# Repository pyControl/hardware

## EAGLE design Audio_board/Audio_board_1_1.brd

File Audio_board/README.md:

# Audio board

An audio amplifier board for driving a speaker to produce auditory stimuli. The board uses the micropython DAC for stimulus generation. The audio board must be plugged into a port on the breakout board which supports DAC output and I2C serial communication (used to set the volume). Up to two audio boards can be used with a single breakout board allowing two speakers to be driven independently.

[documentation](https://pycontrol.readthedocs.io/en/latest/user-guide/hardware/#audio-board)

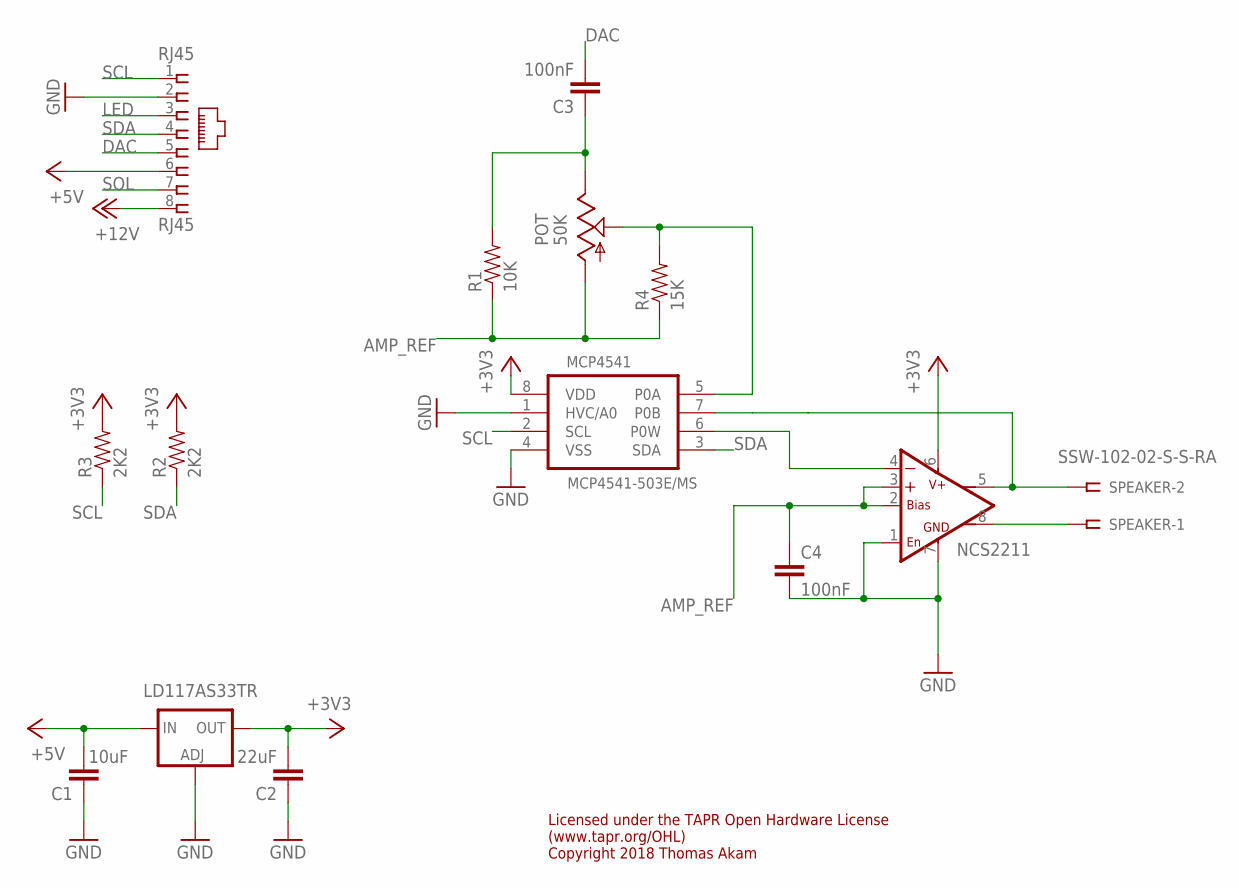
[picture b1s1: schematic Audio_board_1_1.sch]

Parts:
C1: 10uF; C1206
C2: 22uF; C1206
C3, C4: 100nF; C0805
LD117: LD117AS33TR; SOT223
MCP4541: MCP4541-503E/MS; SOP65P490X110-8N
NCS2211: NCS22111M; SO08
POT: 50K; RS3
R1: 10K; 0805
R2, R3: 2K2; 0805
R4: 15K; 0805
RJ45: RJ45; RJ45-NO-SHIELD-VERTICAL
SPEAKER: SSW-102-02-S-S-RA

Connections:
+3V3: C2.2, LD117.4 (OUT), MCP4541.8 (VDD), NCS2211.6 (VS), R2.2, R3.2
+5V: C1.2, LD117.3 (IN), RJ45.6
+12V: RJ45.8
AMP_REF: C4.1, NCS2211.2 (BIAS), NCS2211.3 (+IN), POT.A, R1.1, R4.1
DAC: C3.2, RJ45.5
GND: C1.1, C2.1, C4.2, LD117.1 (ADJ), MCP4541.1 (HVC/A0), MCP4541.4 (VSS), NCS2211.1 (ENABLE), NCS2211.7 (GND), RJ45.2
LED: RJ45.3
unnamed: NCS2211.8 (-OUT), SPEAKER.1
SCL: MCP4541.2 (SCL), R3.1, RJ45.1
SDA: MCP4541.3 (SDA), R2.1, RJ45.4
SIG1: C3.1, POT.E, R1.2
SIG2: MCP4541.5 (P0A), POT.S, R4.2
SIG3: MCP4541.6 (P0W), NCS2211.4 (-IN)
SOL: RJ45.7
SPEAKER+: MCP4541.7 (P0B), NCS2211.5 (+OUT), SPEAKER.2

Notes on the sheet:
Licensed under the TAPR Open Hardware License (www.tapr.org/OHL) Copyright 2018 Thomas Akam

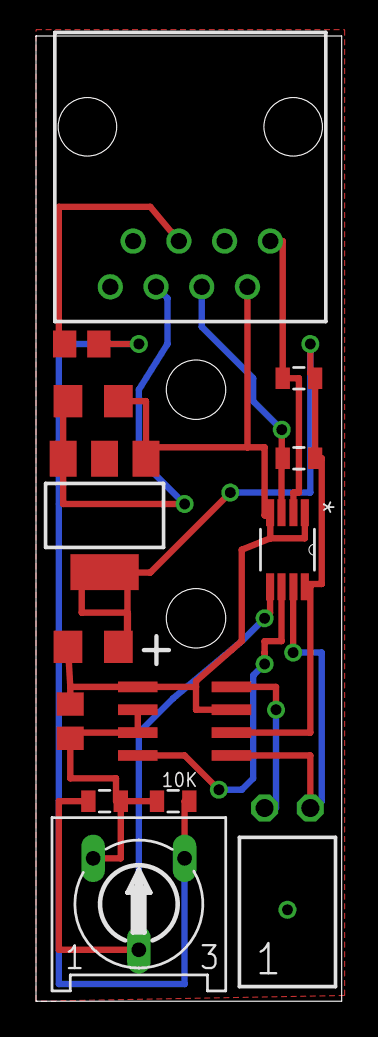
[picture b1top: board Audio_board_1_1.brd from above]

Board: 2 copper layers, 17.0 x 53.6 mm, 14 parts (0 on the bottom side), 12 nets.

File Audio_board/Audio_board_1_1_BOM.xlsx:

Part | Value | Device | Package | Description | MF | MPN | OC_FARNELL
C1 | 10uF | - | 1206 | Capacitor | MULTICOMP | MC1206X106K160CT | 2112752
C2 | 22uF | - | 1206 | Capacitor | KEMET | T491A226K010AT | 1457420
C3 | 100nF | - | 0805 | Capacitor | MULTICOMP | MC0805B104K500CT | 1759265
C4 | 100nF | - | 0805 | Capacitor | MULTICOMP | MC0805B104K500CT | 1759265
LD117 | - | AP1117E33G-13 | SOT223 | LDO Vreg | DIODES INC | AP1117E33G-13 | 1825291
MCP4541 | 50K | MCP4541-503E/MS | MSOP8 | Digital POT | MICROCHIP | MCP4541-503E/MS | 1840713
NCS2211 | - | NCS2211DR2G | SO08 | Audio Power Amp | ON SEMICONDUCTOR | NCS2211DR2G | 2464727
R1 | 10K | - | 0805 | Resistor 0805 | BOURNS | CR0805-FX-1002ELF | 1612522
R2 | 2K2 | - | 0805 | Resistor 0805 | Multicomp | MCWR08X2201FTL | 2447623
R3 | 2K2 | - | 0805 | Resistor 0805 | Multicomp | MCWR08X2201FTL | 2447623
R4 | 15K | - | 0805 | Resistor 0805 | Multicomp | MC01W0805115K | 9332618
POT | 50K | - | - | POTENTIOMETER | BOURNS | 3386F-1-503TLF | 9354727
RJ45 | - | RJ45Horisontal | - | RJ45Horisontal | TE CONNECTIVITY | 215877-1 | 3363144
SPKR | - | - | - | 2x1 Receptacle, right angle | SAMTEC | SSW-102-02-T-S-RA | 1803308
Licensed under the TAPR Open Hardware License
(www.tapr.org/OHL)
Copyright 2018 Thomas Akam

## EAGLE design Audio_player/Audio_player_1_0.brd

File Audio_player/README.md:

# Audio player

An audio board for pyControl which uses a [DF player](https://www.dfrobot.com/wiki/index.php/DFPlayer_Mini_SKU:DFR0299) module to play wav files from an SD card. The board has two speaker outputs which can be independently enabled/disabled, allowing stereo wav files to be played, or mono wav files to be played from either or both speakers. 

[Documentation](https://pycontrol.readthedocs.io/en/latest/user-guide/hardware/#audio_player)

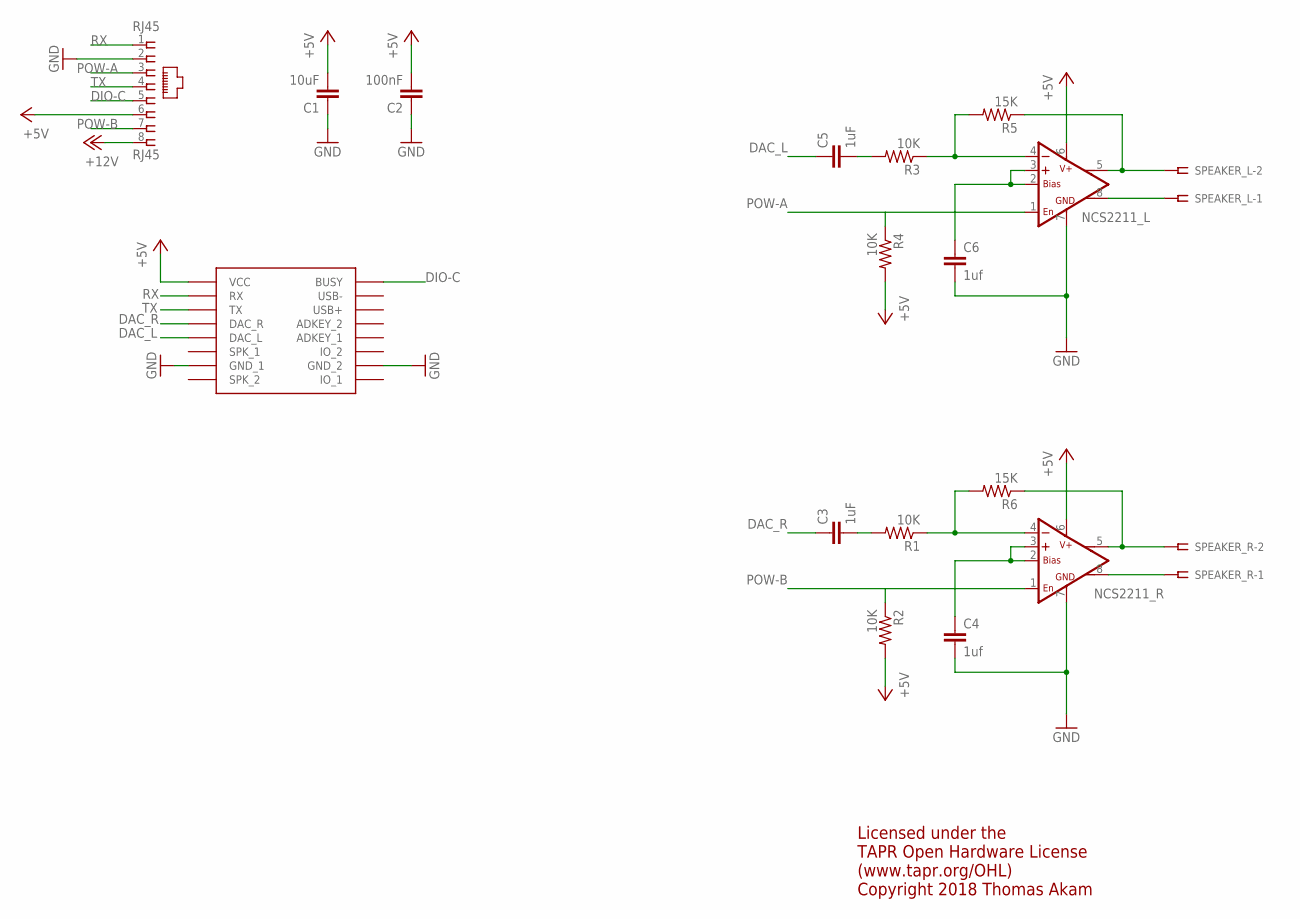
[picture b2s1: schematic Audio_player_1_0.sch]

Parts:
C1: 10uF; C0805
C2: 100nF; C0805
C3, C5: 1uF; C0805
C4, C6: 1uf; C0805
NCS2211_L, NCS2211_R: NCS22111M; SO08
R1, R2, R3, R4: 10K; 0805
R5, R6: 15K; 0805
RJ45: RJ45; RJ45-NO-SHIELD-VERTICAL
SPEAKER_L: SSW-102-02-S-S-RA
SPEAKER_R: SSW-102-02-S-S-RA
U$1: DFPLAYER

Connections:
+5V: C1.2, C2.2, NCS2211_L.6 (VS), NCS2211_R.6 (VS), R2.2, R4.2, RJ45.6, U$1.VCC
+12V: RJ45.8
AMP_REF: C4.1, NCS2211_R.2 (BIAS), NCS2211_R.3 (+IN)
AMP_REF1: C6.1, NCS2211_L.2 (BIAS), NCS2211_L.3 (+IN)
DAC_L: C5.1, U$1.DAC_L
DAC_R: C3.1, U$1.DAC_R
DIO-C: RJ45.5, U$1.BUSY
GND: C1.1, C2.1, C4.2, C6.2, NCS2211_L.7 (GND), NCS2211_R.7 (GND), RJ45.2, U$1.GND_1, U$1.GND_2
unnamed: NCS2211_L.8 (-OUT), SPEAKER_L.1
unnamed: NCS2211_R.8 (-OUT), SPEAKER_R.1
unnamed: C3.2, R1.2
unnamed: C5.2, R3.2
POW-A: NCS2211_L.1 (ENABLE), R4.1, RJ45.3
POW-B: NCS2211_R.1 (ENABLE), R2.1, RJ45.7
RX: RJ45.1, U$1.RX
SIG1: NCS2211_L.4 (-IN), R3.1, R5.2
SIG3: NCS2211_R.4 (-IN), R1.1, R6.2
SPEAKER+: NCS2211_R.5 (+OUT), R6.1, SPEAKER_R.2
SPEAKER+1: NCS2211_L.5 (+OUT), R5.1, SPEAKER_L.2
TX: RJ45.4, U$1.TX

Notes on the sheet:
Licensed under the TAPR Open Hardware License (www.tapr.org/OHL) Copyright 2018 Thomas Akam

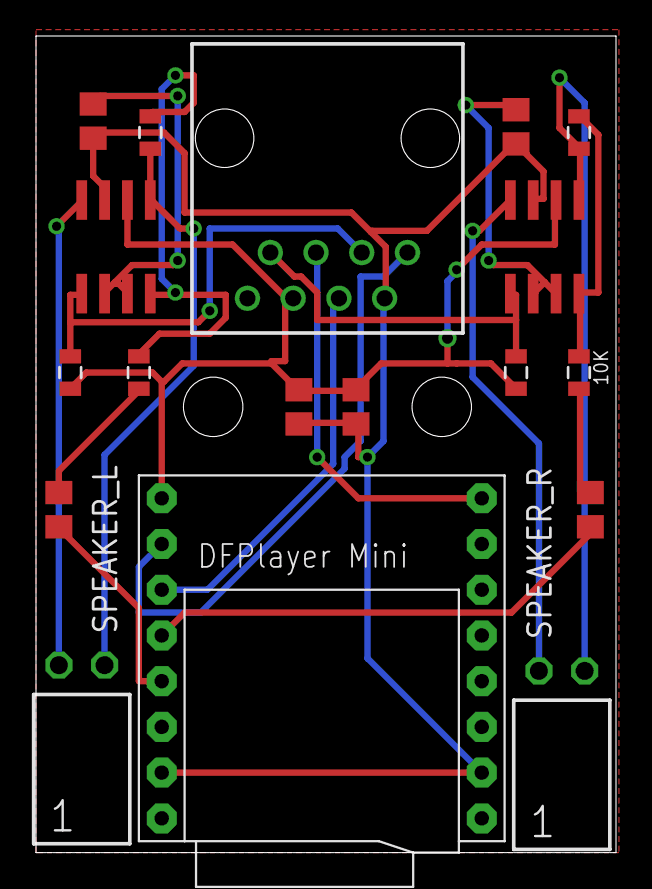
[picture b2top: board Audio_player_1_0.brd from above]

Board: 2 copper layers, 32.2 x 45.4 mm, 18 parts (0 on the bottom side), 19 nets.

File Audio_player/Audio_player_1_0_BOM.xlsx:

Part | Value | Device | Package | Description | MF | MPN | OC_FARNELL
C1 | 10uF | - | 0805 | Capacitor | MURATA | GCM21BR70J106KE22L | 2470434
C2 | 100nF | - | 0805 | Capacitor | MULTICOMP | MC0805B104K500CT | 1759265
C3 | 1uF | - | 0805 | Capacitor | MULTICOMP | MC0805B105K100CT | 2320857
C4 | 1uF | - | 0805 | Capacitor | MULTICOMP | MC0805B105K100CT | 2320857
C5 | 1uF | - | 0805 | Capacitor | MULTICOMP | MC0805B105K100CT | 2320857
C5 | 1uF | - | 0805 | Capacitor | MULTICOMP | MC0805B105K100CT | 2320857
R1 | 10K | - | 0805 | Resistor | MULTICOMP | MCWR08X1002FTL | 2447553
R2 | 10K | - | 0805 | Resistor | MULTICOMP | MCWR08X1002FTL | 2447553
R3 | 10K | - | 0805 | Resistor | MULTICOMP | MCWR08X1002FTL | 2447553
R4 | 10K | - | 0805 | Resistor | MULTICOMP | MCWR08X1002FTL | 2447553
R5 | 15K | - | 0805 | Resistor | MULTICOMP | MCWR08X1502FTL | 2447575
R6 | 15K | - | 0805 | Resistor | MULTICOMP | MCWR08X1502FTL | 2447575
NCS2211_L | - | NCS2211DR2G | SO08 | Audio Power Amp | ON SEMICONDUCTOR | NCS2211DR2G | 2464727
NCS2211_R | - | NCS2211DR2G | SO08 | Audio Power Amp | ON SEMICONDUCTOR | NCS2211DR2G | 2464727
RJ45 |  | - | - | RJ45 con. vertical | TE CONNECTIVITY | 5556416-1 | 1773034
SPEAKER_L | - | - | - | 2x1 Receptacle, right angle | SAMTEC | SSW-102-02-T-S-RA | 1803308
SPEAKER_R | - | - | - | 2x1 Receptacle, right angle | SAMTEC | SSW-102-02-T-S-RA | 1803308
DFPLAYER_CON_1 | - | - | - | 8 Way female header | MULTICOMP | 2212S-08SG-85 | 1593463
DFPLAYER_CON_2 | - | - | - | 8 Way female header | MULTICOMP | 2212S-08SG-85 | 1593463
DFPlayer | - | - | - | DFPlayer module | DFRobot | DFR0299 | -
Licensed under the TAPR Open Hardware License
(www.tapr.org/OHL)
Copyright 2018 Thomas Akam

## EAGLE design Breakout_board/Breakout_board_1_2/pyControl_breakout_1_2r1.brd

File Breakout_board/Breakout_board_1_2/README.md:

# Breakout board 1.2

This folder contains design files for version 1.2 of the pyControl breakout board.

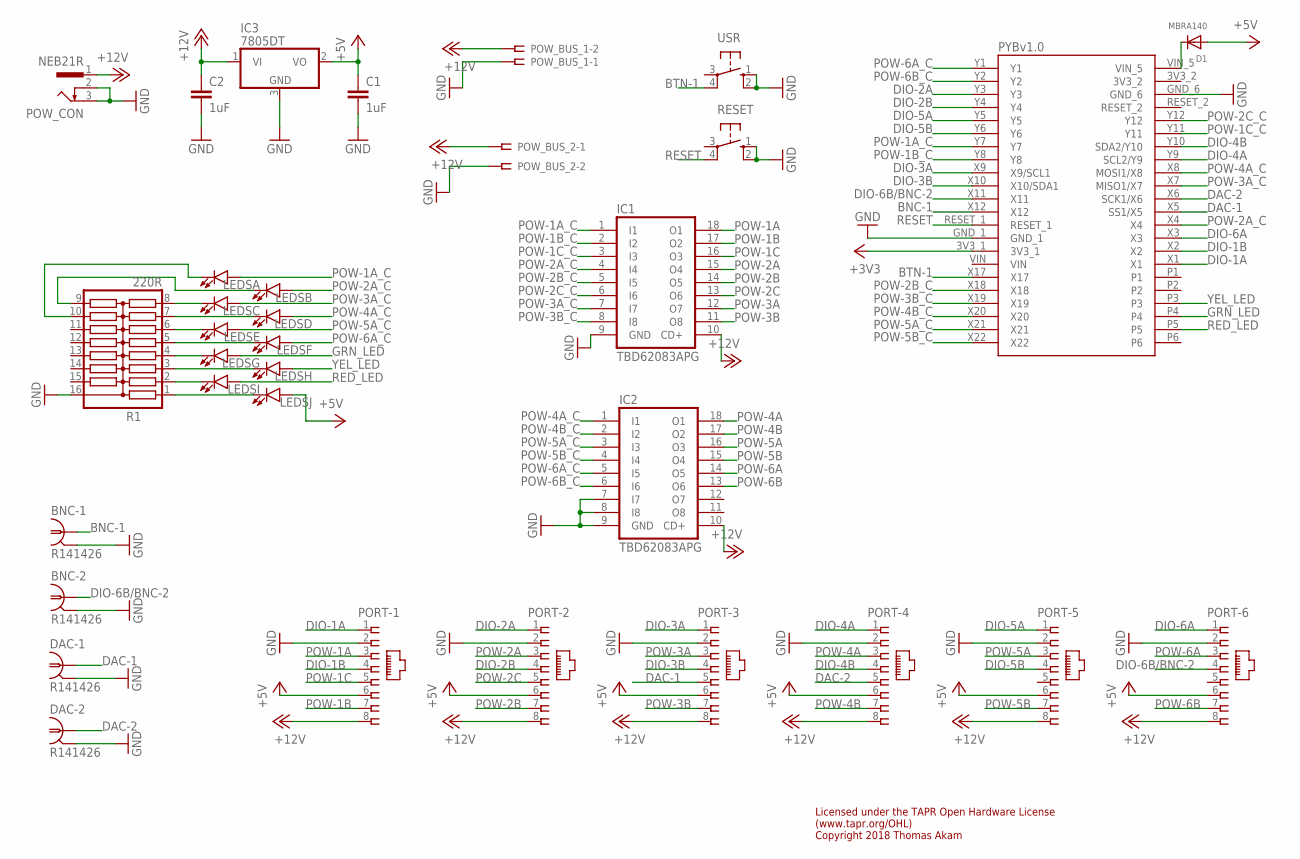
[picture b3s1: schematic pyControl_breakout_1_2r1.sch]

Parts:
BNC-1, BNC-2: R141426
C1, C2: 1uF; C1206
D1: MBRA140; SOD-123
DAC-1, DAC-2: R141426
IC1, IC2: TBD62083APG; DIL18
IC3: 7805DT; TO252
LEDS: LED_BARGRAPH_10; LED_BARGAPH_10
PORT-1, PORT-2, PORT-3, PORT-4, PORT-5, PORT-6: RJ45VERTICAL; RJ45-NO-SHIELD-VERTICAL
POW_BUS_1, POW_BUS_2: SSW-102-02-S-S-RA
POW_CON: NEB21R
PYBOARD: PYBOARD-REDUCED-2
R1: 220R; SO16
RESET: 40-XX; B3F-40XX; MPN B3F-4000
USR: 40-XX; B3F-40XX

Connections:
+3V3: PYBOARD.3V3_1
+5V: C1.1, D1.A, IC3.2 (VO), LEDS.10 (A), PORT-1.6, PORT-2.6, PORT-3.6, PORT-4.6, PORT-5.6, PORT-6.6
+12V: C2.1, IC1.10 (CD+), IC2.10 (CD+), IC3.1 (VI), PORT-1.8, PORT-2.8, PORT-3.8, PORT-4.8, PORT-5.8, PORT-6.8, POW_BUS_1.2, POW_BUS_2.1, POW_CON.1
BNC-1: BNC-1.1, PYBOARD.X12
BTN-1: PYBOARD.X17, USR.4 (P1)
DAC-1: DAC-1.1, PORT-3.5, PYBOARD.X5 (SS1/X5)
DAC-2: DAC-2.1, PORT-4.5, PYBOARD.X6 (SCK1/X6)
DIO-1A: PORT-1.1, PYBOARD.X1
DIO-1B: PORT-1.4, PYBOARD.X2
DIO-2A: PORT-2.1, PYBOARD.Y3
DIO-2B: PORT-2.4, PYBOARD.Y4
DIO-3A: PORT-3.1, PYBOARD.X9 (X9/SCL1)
DIO-3B: PORT-3.4, PYBOARD.X10 (X10/SDA1)
DIO-4A: PORT-4.1, PYBOARD.Y9 (SCL2/Y9)
DIO-4B: PORT-4.4, PYBOARD.Y10 (SDA2/Y10)
DIO-5A: PORT-5.1, PYBOARD.Y5
DIO-5B: PORT-5.4, PYBOARD.Y6
DIO-6A: PORT-6.1, PYBOARD.X3
DIO-6B/BNC-2: BNC-2.1, PORT-6.4, PYBOARD.X11
GND: BNC-1.2 (GND), BNC-1.3 (GND), BNC-1.4 (GND), BNC-1.5 (GND), BNC-2.2 (GND), BNC-2.3 (GND), BNC-2.4 (GND), BNC-2.5 (GND), C1.2, C2.2, DAC-1.2 (GND), DAC-1.3 (GND), DAC-1.4 (GND), DAC-1.5 (GND), DAC-2.2 (GND), DAC-2.3 (GND), DAC-2.4 (GND), DAC-2.5 (GND), IC1.9 (GND), IC2.7 (I7), IC2.8 (I8), IC2.9 (GND), IC3.3 (GND), PORT-1.2, PORT-2.2, PORT-3.2, PORT-4.2, PORT-5.2, PORT-6.2, POW_BUS_1.1, POW_BUS_2.2, POW_CON.2, POW_CON.3, PYBOARD.GND_1, PYBOARD.GND_6, R1.16, RESET.1 (S), RESET.2 (S1), USR.1 (S), USR.2 (S1)
GRN_LED: LEDS.7 (A), PYBOARD.P4
unnamed: LEDS.12 (C), R1.2
unnamed: LEDS.19 (C), R1.9
unnamed: LEDS.18 (C), R1.8
unnamed: LEDS.17 (C), R1.7
unnamed: LEDS.16 (C), R1.6
unnamed: LEDS.15 (C), R1.5
unnamed: LEDS.14 (C), R1.4
unnamed: LEDS.13 (C), R1.3
unnamed: LEDS.20 (C), R1.10
unnamed: LEDS.11 (C), R1.1
unnamed: D1.C, PYBOARD.VIN_5
POW-1A: IC1.18 (O1), PORT-1.3
POW-1A_C: IC1.1 (I1), LEDS.1 (A), PYBOARD.Y7
POW-1B: IC1.17 (O2), PORT-1.7
POW-1B_C: IC1.2 (I2), PYBOARD.Y8
POW-1C: IC1.16 (O3), PORT-1.5
POW-1C_C: IC1.3 (I3), PYBOARD.Y11
POW-2A: IC1.15 (O4), PORT-2.3
POW-2A_C: IC1.4 (I4), LEDS.2 (A), PYBOARD.X4
POW-2B: IC1.14 (O5), PORT-2.7
POW-2B_C: IC1.5 (I5), PYBOARD.X18
POW-2C: IC1.13 (O6), PORT-2.5
POW-2C_C: IC1.6 (I6), PYBOARD.Y12
POW-3A: IC1.12 (O7), PORT-3.3
POW-3A_C: IC1.7 (I7), LEDS.3 (A), PYBOARD.X7 (MISO1/X7)
POW-3B: IC1.11 (O8), PORT-3.7
POW-3B_C: IC1.8 (I8), PYBOARD.X19
POW-4A: IC2.18 (O1), PORT-4.3
POW-4A_C: IC2.1 (I1), LEDS.4 (A), PYBOARD.X8 (MOSI1/X8)
POW-4B: IC2.17 (O2), PORT-4.7
POW-4B_C: IC2.2 (I2), PYBOARD.X20
POW-5A: IC2.16 (O3), PORT-5.3
POW-5A_C: IC2.3 (I3), LEDS.5 (A), PYBOARD.X21
POW-5B: IC2.15 (O4), PORT-5.7
POW-5B_C: IC2.4 (I4), PYBOARD.X22
POW-6A: IC2.14 (O5), PORT-6.3
POW-6A_C: IC2.5 (I5), LEDS.6 (A), PYBOARD.Y1
POW-6B: IC2.13 (O6), PORT-6.7
POW-6B_C: IC2.6 (I6), PYBOARD.Y2
RED_LED: LEDS.9 (A), PYBOARD.P5
RESET: PYBOARD.RESET_1, RESET.4 (P1)
YEL_LED: LEDS.8 (A), PYBOARD.P3

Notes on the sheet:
Licensed under the TAPR Open Hardware License (www.tapr.org/OHL) Copyright 2018 Thomas Akam

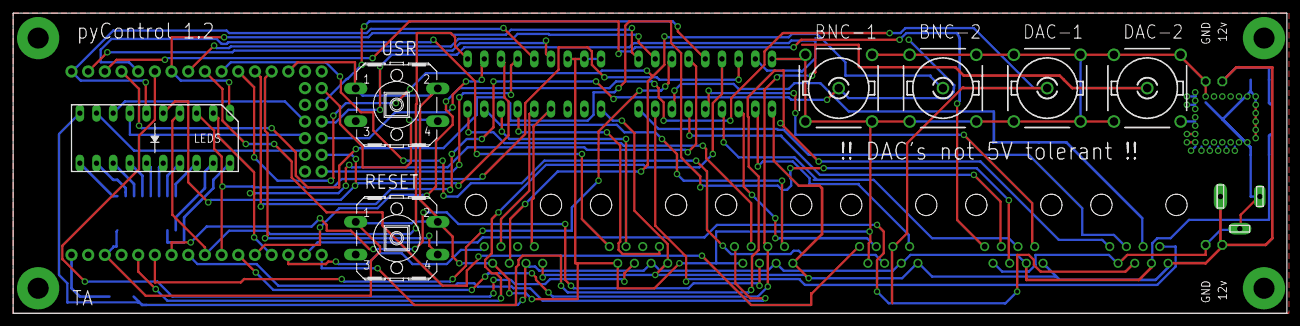
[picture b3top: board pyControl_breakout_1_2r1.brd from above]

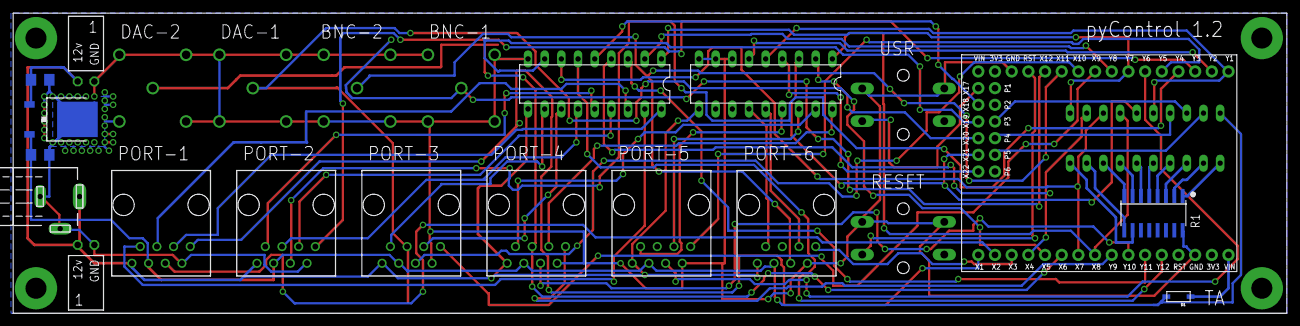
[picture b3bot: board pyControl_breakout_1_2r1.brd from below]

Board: 2 copper layers, 194.0 x 45.7 mm, 24 parts (17 on the bottom side), 62 nets.

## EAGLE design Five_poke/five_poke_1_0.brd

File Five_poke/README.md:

# Five poke

**Assembled**

**PCB**

A set of five nose-pokes mounted in a row on a single PCB and controlled via two behaviour ports.  Each poke consists of an infra-red beam and a stimulus LED that illuminates the back of the poke.

[Documentation](https://pycontrol.readthedocs.io/en/latest/user-guide/hardware/#five-poke)

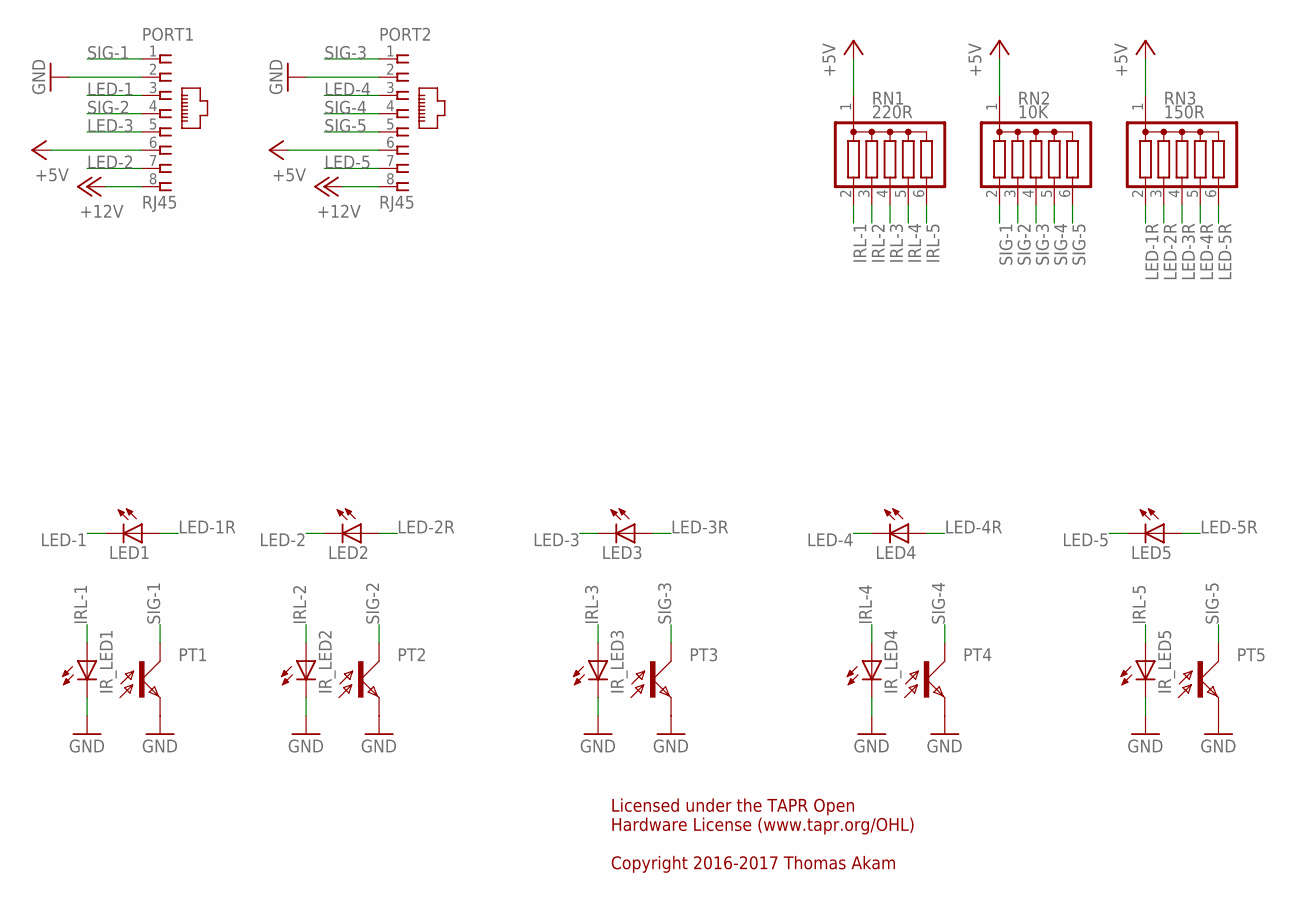
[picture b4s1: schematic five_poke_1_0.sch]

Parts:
IR_LED1, IR_LED2, IR_LED3, IR_LED4, IR_LED5: LEDIRL80A; IRL80A
LED1, LED2, LED3, LED4, LED5: LEDSML0805; SML0805
PORT1, PORT2: RJ45; RJ45-NO-SHIELD-VERTICAL
PT1, PT2, PT3, PT4, PT5: LPT80A
RN1: 220R; SIL6
RN2: 10K; SIL6
RN3: 150R; SIL6

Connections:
+5V: PORT1.6, PORT2.6, RN1.1, RN2.1, RN3.1
+12V: PORT1.8, PORT2.8
GND: IR_LED1.K (C), IR_LED2.K (C), IR_LED3.K (C), IR_LED4.K (C), IR_LED5.K (C), PORT1.2, PORT2.2, PT1.E, PT2.E, PT3.E, PT4.E, PT5.E
IRL-1: IR_LED1.A, RN1.2
IRL-2: IR_LED2.A, RN1.3
IRL-3: IR_LED3.A, RN1.4
IRL-4: IR_LED4.A, RN1.5
IRL-5: IR_LED5.A, RN1.6
LED-1: LED1.C, PORT1.3
LED-1R: LED1.A, RN3.2
LED-2: LED2.C, PORT1.7
LED-2R: LED2.A, RN3.3
LED-3: LED3.C, PORT1.5
LED-3R: LED3.A, RN3.4
LED-4: LED4.C, PORT2.3
LED-4R: LED4.A, RN3.5
LED-5: LED5.C, PORT2.7
LED-5R: LED5.A, RN3.6
SIG-1: PORT1.1, PT1.C, RN2.2
SIG-2: PORT1.4, PT2.C, RN2.3
SIG-3: PORT2.1, PT3.C, RN2.4
SIG-4: PORT2.4, PT4.C, RN2.5
SIG-5: PORT2.5, PT5.C, RN2.6

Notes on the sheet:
Licensed under the TAPR Open Hardware License (www.tapr.org/OHL) Copyright 2016-2017 Thomas Akam

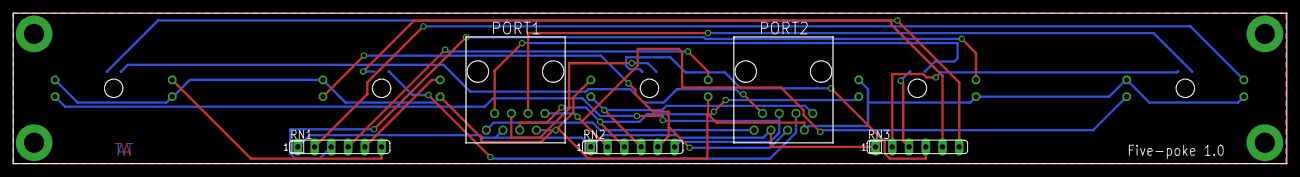
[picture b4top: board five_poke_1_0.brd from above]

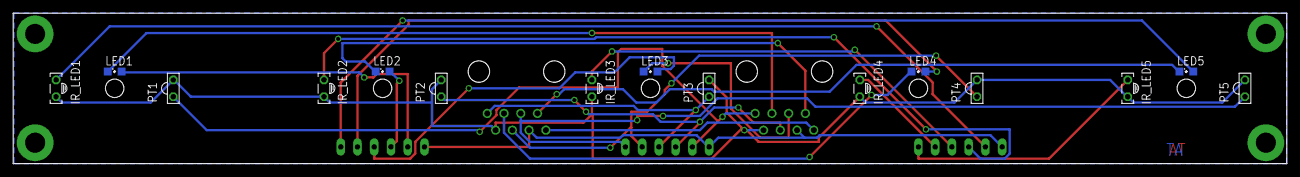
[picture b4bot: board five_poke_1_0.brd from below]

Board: 2 copper layers, 193.2 x 22.8 mm, 20 parts (15 on the bottom side), 23 nets.

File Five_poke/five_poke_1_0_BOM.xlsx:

Part | Value | Device | Package | Description | MF | MPN | OC_FARNELL
IR_LED1 |  | - | - | IR LED side | Sharp | GL480E00000F | 9707794
IR_LED2 |  | - | - | IR LED side | Sharp | GL480E00000F | 9707794
IR_LED3 |  | - | - | IR LED side | Sharp | GL480E00000F | 9707794
IR_LED4 |  | - | - | IR LED side | Sharp | GL480E00000F | 9707794
IR_LED5 |  | - | - | IR LED side | Sharp | GL480E00000F | 9707794
LED1 |  | - | 0805 | LED white 0805 | MULTICOMP | OVS-0801 | 1716764
LED2 |  | - | 0805 | LED white 0805 | MULTICOMP | OVS-0801 | 1716764
LED3 |  | - | 0805 | LED white 0805 | MULTICOMP | OVS-0801 | 1716764
LED4 |  | - | 0805 | LED white 0805 | MULTICOMP | OVS-0801 | 1716764
LED5 |  | - | 0805 | LED white 0805 | MULTICOMP | OVS-0801 | 1716764
PORT1 |  | - | - | RJ45VERTICAL | TE CONNECTIVITY | 5556416-1 | 1773034
PORT2 |  | - | - | RJ45VERTICAL | TE CONNECTIVITY | 5556416-1 | 1773034
PT1 |  | - | - | PHOTO TRANSISTOR | OSRAM | SFH3100F-1-Z | 1226443
PT2 |  | - | - | PHOTO TRANSISTOR | OSRAM | SFH3100F-1-Z | 1226443
PT3 |  | - | - | PHOTO TRANSISTOR | OSRAM | SFH3100F-1-Z | 1226443
PT4 |  | - | - | PHOTO TRANSISTOR | OSRAM | SFH3100F-1-Z | 1226443
PT5 |  | - | - | PHOTO TRANSISTOR | OSRAM | SFH3100F-1-Z | 1226443
RN1 | 220R | - | SIL6 | Resistor network | BOURNS | 4606X-101-221LF | 9356185
RN2 | 10K | - | SIL6 | Resistor network | BOURNS | 4606X-101-103LF | 9356142
RN3 | 150R | - | SIL6 | Resistor network | BOURNS | 4606X-101-151LF | -
Licensed under the TAPR Open Hardware License (www.tapr.org/OHL)
Copyright 2016-2017 Thomas Akam

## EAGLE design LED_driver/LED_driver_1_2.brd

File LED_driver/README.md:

# LED driver

A constant current LED driver for optogenetic stimulation.  The LED current can be manually adjusted between 0.03 and 0.8A using controls on the board.  The LED driver plugs into any behaviour port on the breakout board.

[Documentation](https://pycontrol.readthedocs.io/en/latest/user-guide/hardware/#led-driver)

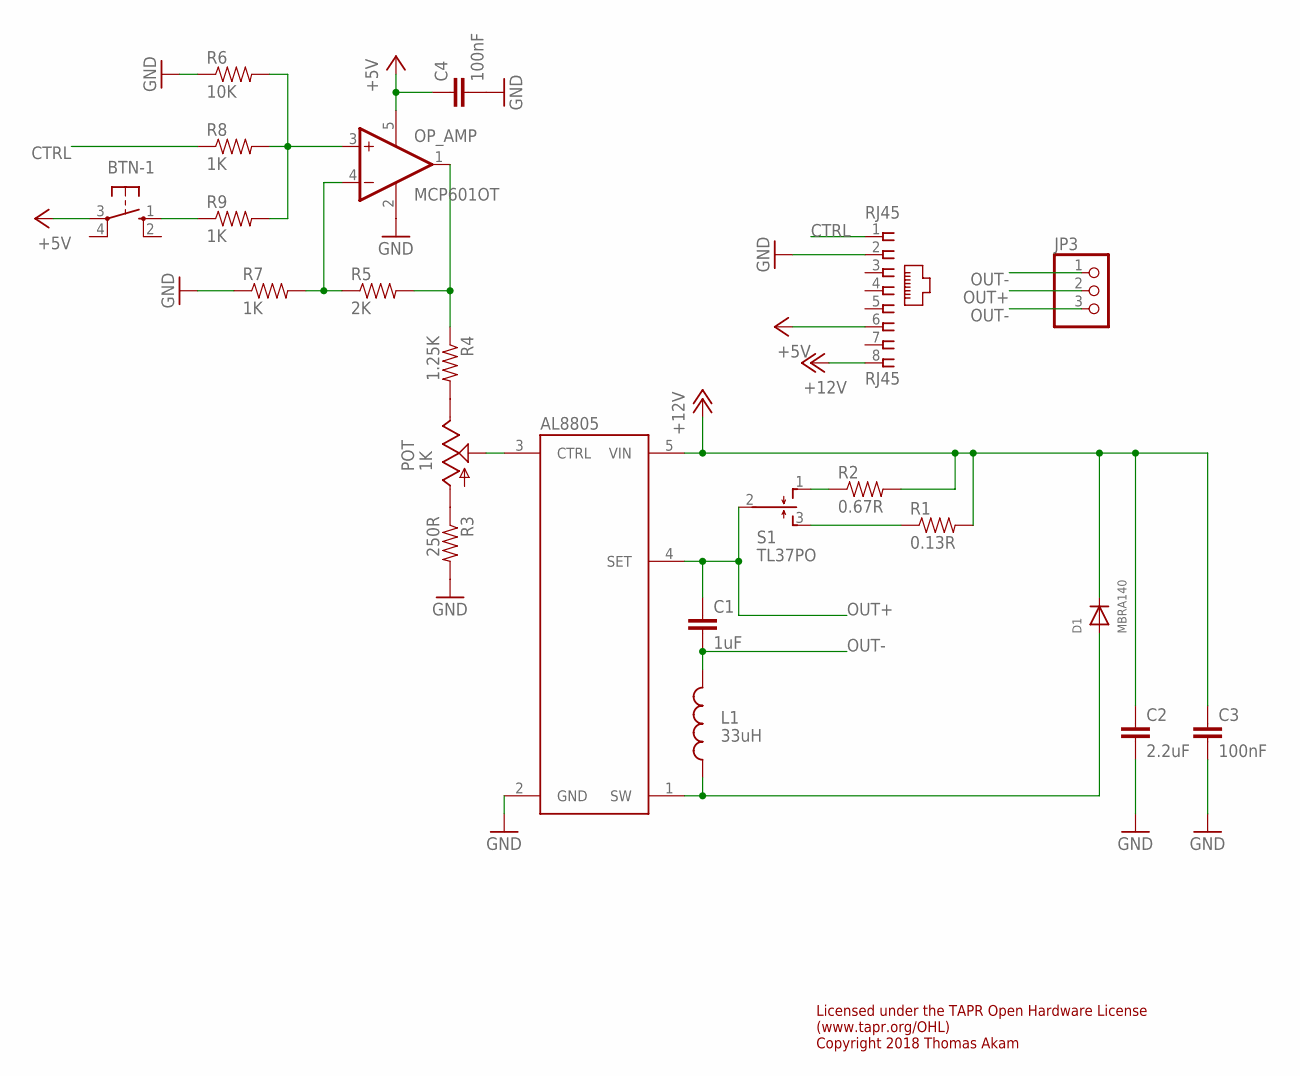
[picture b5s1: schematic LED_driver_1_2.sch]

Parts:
AL8805: AL8805; SOT23-5
BTN-1: 10-XX; B3F-10XX
C1: 1uF; C0805
C2: 2.2uF; C0805
C3, C4: 100nF; C0805
D1: MBRA140; SOD-123
JP3: PINHD-1X3; 1X03
L1: 33uH; SRN6045
OP_AMP: MCP601OT; SOT23-5
POT: 1K; RS3
R1: 0.13R; 0805
R2: 0.67R; 0805
R3: 250R; 0805
R4: 1.25K; 0805
R5: 2K; 0805
R6: 10K; 0805
R7, R8, R9: 1K; 0805
RJ45: RJ45; RJ45-NO-SHIELD-VERTICAL
S1: TL37PO; TL3XPO

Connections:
+5V: BTN-1.3, C4.1, OP_AMP.5 (V+), RJ45.6
+12V: AL8805.5 (VIN), C2.1, C3.1, D1.C, R1.2, R2.2, RJ45.8
CTRL: R8.1, RJ45.1
GND: AL8805.2 (GND), C2.2, C3.2, C4.2, OP_AMP.2 (V-), R3.2, R6.1, R7.1, RJ45.2
unnamed: AL8805.3 (CTRL), POT.S
unnamed: POT.A, R3.1
unnamed: POT.E, R4.2
unnamed: R2.1, S1.1 (O)
unnamed: R1.1, S1.3 (S)
unnamed: OP_AMP.1 (OUT), R4.1, R5.2
unnamed: OP_AMP.4 (-IN), R5.1, R7.2
unnamed: OP_AMP.3 (+IN), R6.2, R8.2, R9.2
unnamed: BTN-1.1 (S), R9.1
OUT+: AL8805.4 (SET), C1.1, JP3.2, S1.2
OUT-: C1.2, JP3.1, JP3.3, L1.2
SW: AL8805.1 (SW), D1.A, L1.1

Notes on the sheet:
Licensed under the TAPR Open Hardware License (www.tapr.org/OHL) Copyright 2018 Thomas Akam

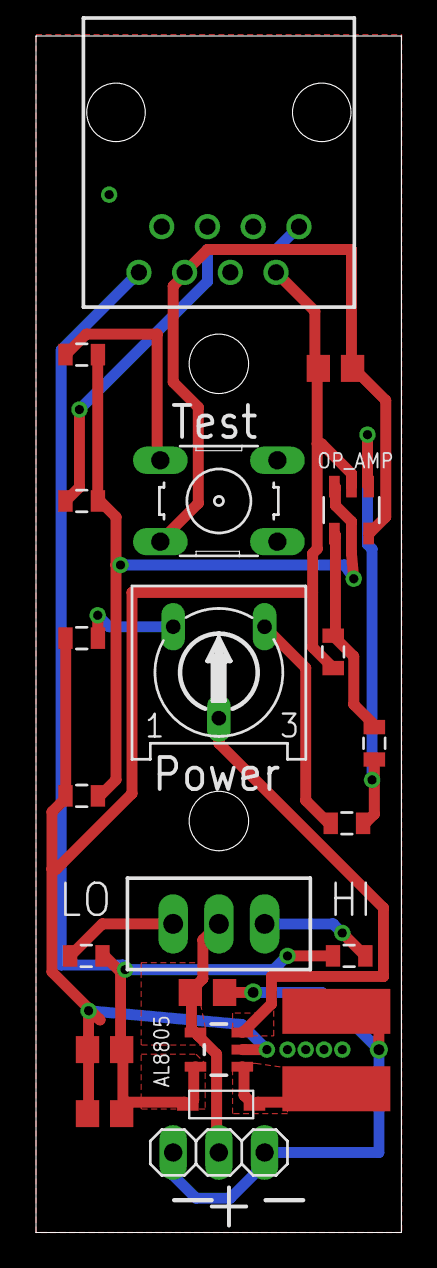
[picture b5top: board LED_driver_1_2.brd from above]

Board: 2 copper layers, 20.3 x 66.5 mm, 22 parts (0 on the bottom side), 16 nets.

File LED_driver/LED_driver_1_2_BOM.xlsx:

Part | Value | Device | Package | Description | MF | MPN | OC_FARNELL
AL8805 | - | AL8805 | SOT23-5 | LED driver | Diodes inc. | AL8805W5-7 | 1904023
BTN-1 | - | B3F-1000 | B3F-1000 | Pushbutton | OMRON | B3F-1000 | 176432
C1 | 1uF | - | 0805 | Capacitor | MULTICOMP | MC0805B105K250CT | 176432
C2 | 2.2uF | - | 0805 | Capacitor | MULTICOMP | MC0805B225K250CT | 2320829
C3 | 100nF | - | 0805 | Capacitor | MULTICOMP | MC0805B104K500CT | 1759265
C4 | 100nF | - | 0805 | Capacitor | MULTICOMP | MC0805B104K500CT | 1759265
D1 | - | - | SOD-123FL | DIODE | ON SEMICONDUCTOR | MBR120VLSFT3G | 2533227
L1 | 33uH | - | SRN6045 | Inductor | BOURNS | SRN6045-330M | 2061655
OP_AMP | - | - | SOT23-5 | Op Amp | Microchip | MCP6001T-I/OT | 4974992
POT | 1K | - | - | Potentiometer | BOURNS | 3386F-1-102TLF | 9354549
R1 | 0.13R | - | 0805 | Resistor 0805 | Panasonic | ERJS6SFR13V | 2381097
R2 | 0.67R | - | 0805 | Resistor 0805 | Yageo | RL0805FR-7W0R68L | 8067759
R3 | 250R | - | 0805 | Resistor 0805 | Multicomp | MC01W08051249R | 2141762
R4 | 1.25K | - | 0805 | Resistor 0805 | Panasonic | ERJ6ENF1241V | 2303560
R5 | 2K | - | 0805 | Resistor 0805 | Panasonic | ERJ6ENF2001V | 2057613
R6 | 10K | - | 0805 | Resistor 0805 | BOURNS | CR0805-FX-1002ELF | 1612522
R7 | 1K | - | 0805 | Resistor 0805 | Welwyn | WCR0805-1K0FI | 1099800
R8 | 1K | - | 0805 | Resistor 0805 | Welwyn | WCR0805-1K0FI | 1099800
R9 | 1K | - | 0805 | Resistor 0805 | Welwyn | WCR0805-1K0FI | 1099800
S1 | - | - | - | Switch SPDT | Wurth Elektronik | 450301014042 | 2134452
RJ45 | - | RJ45Horisontal | - | RJ45Horisontal | TE CONNECTIVITY | 215877-1 | 3363144
JP3 | - | - | - | 1x3 Receptacle | Multicomp | 2212S-03SG-85 | 1593459
Licensed under the TAPR Open Hardware License
(www.tapr.org/OHL)
Copyright 2018 Thomas Akam

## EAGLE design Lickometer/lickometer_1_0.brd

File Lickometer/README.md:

# Lickometer

An electrical lickometer board with has two lick detection circuits and two ports for controlling 12V solenoids.

[Documentation](https://pycontrol.readthedocs.io/en/latest/user-guide/hardware/#lickometer)

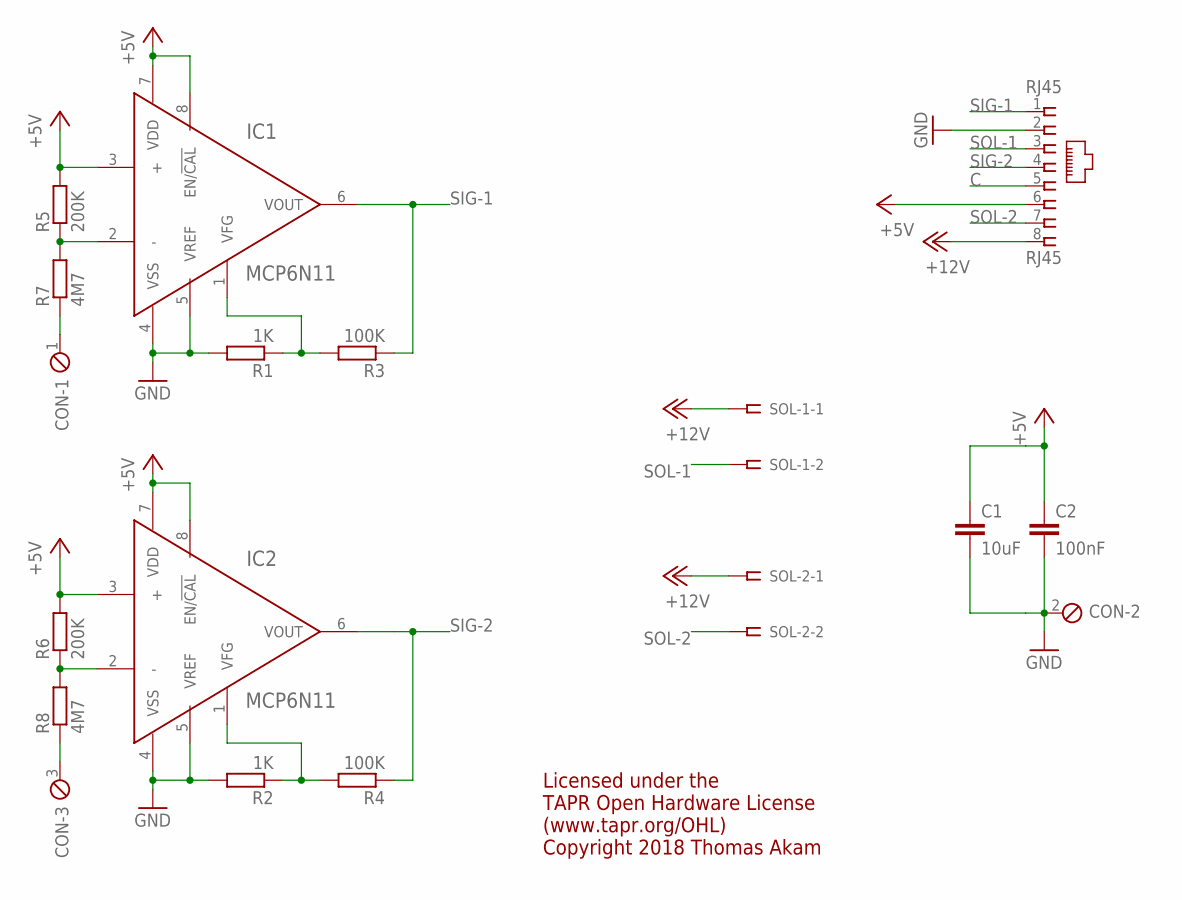
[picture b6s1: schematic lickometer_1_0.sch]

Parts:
C1: 10uF; C1206
C2: 100nF; C0805
CON: MPT3; 3POL254
IC1, IC2: MCP6N11; SOIC127P600X175-8N
R1, R2: 1K; R0805
R3, R4: 100K; R0805
R5, R6: 200K; R0805
R7, R8: 4M7; R0805
RJ45: RJ45; RJ45-NO-SHIELD-VERTICAL
SOL-1, SOL-2: SSW-102-02-S-S-RA

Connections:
+5V: C1.1, C2.1, IC1.3 (+), IC1.7 (VDD), IC1.8 (EN/!CAL!), IC2.3 (+), IC2.7 (VDD), IC2.8 (EN/!CAL!), R5.2, R6.2, RJ45.6
+12V: RJ45.8, SOL-1.1, SOL-2.1
C: RJ45.5
GND: C1.2, C2.2, CON.2, IC1.4 (VSS), IC1.5 (VREF), IC2.4 (VSS), IC2.5 (VREF), R1.2, R2.2, RJ45.2
unnamed: IC2.2 (-), R6.1, R8.2
unnamed: CON.3, R8.1
unnamed: IC1.2 (-), R5.1, R7.2
unnamed: CON.1, R7.1
unnamed: IC1.1 (VFG), R1.1, R3.2
unnamed: IC2.1 (VFG), R2.1, R4.2
SIG-1: IC1.6 (VOUT), R3.1, RJ45.1
SIG-2: IC2.6 (VOUT), R4.1, RJ45.4
SOL-1: RJ45.3, SOL-1.2
SOL-2: RJ45.7, SOL-2.2

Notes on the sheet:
Licensed under the TAPR Open Hardware License (www.tapr.org/OHL) Copyright 2018 Thomas Akam

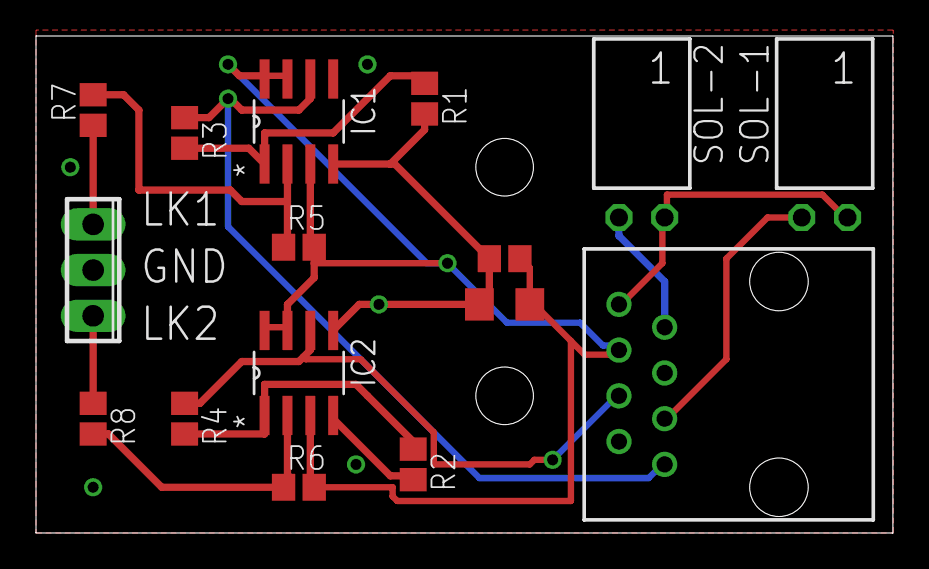
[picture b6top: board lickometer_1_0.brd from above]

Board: 2 copper layers, 47.6 x 27.6 mm, 16 parts (0 on the bottom side), 13 nets.

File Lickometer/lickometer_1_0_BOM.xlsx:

Part | Value | Device | Package | Description | MF | MPN | OC_FARNELL
IC1 | - | - | SOIC8 | Ins Amp | Microchip | MCP6N11-010E/SN | 2065864
IC2 | - | - | SOIC8 | Ins Amp | Microchip | MCP6N11-010E/SN | 2065864
C1 | 10uF | - | 1206 | Capacitor | MULTICOMP | MC1206X106K160CT | 2112752
C2 | 100nF | - | 0805 | Capacitor | MULTICOMP | MC0805B104K500CT | 1759265
R1 | 1K | - | 0805 | Resistor | MULTICOMP | MCMR08X1001FTL | 2073606
R2 | 1K | - | 0805 | Resistor | MULTICOMP | MCMR08X1001FTL | 2073606
R3 | 100K | - | 0805 | Resistor | MULTICOMP | MCSR08X1003FTL | 2074335
R4 | 100K | - | 0805 | Resistor | MULTICOMP | MCSR08X1003FTL | 2074335
R5 | 200K | - | 0805 | Resistor | MULTICOMP | MCWR08X2003FTL | 2447601
R6 | 200K | - | 0805 | Resistor | MULTICOMP | MCWR08X2003FTL | 2447601
R7 | 4M7 | - | 0805 | Resistor | MULTICOMP | MCWR08W4704FTL | 2447676
R8 | 4M7 | - | 0805 | Resistor | MULTICOMP | MCWR08W4704FTL | 2447676
RJ45 | - | RJ45Horisontal | - | RJ45Horisontal | TE CONNECTIVITY | 215877-1 | 3363144
SOL-1 | - | - | - | 2x1 Receptacle, right angle | SAMTEC | SSW-102-02-T-S-RA | 1803308
SO2-1 | - | - | - | 2x1 Receptacle, right angle | SAMTEC | SSW-102-02-T-S-RA | 1803308
CON | - | - | - | Screw terminal 3 way | TE CONNECTIVITY | 282834-3 | 2396254
Licensed under the TAPR Open Hardware License
(www.tapr.org/OHL)
Copyright 2018 Thomas Akam

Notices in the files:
parts and their libraries:
SparkFun-Resistors: Licensing: CC v3.0 Share-Alike You are welcome to use this library for commercial purposes.
